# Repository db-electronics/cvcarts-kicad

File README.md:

# Copyright and Disclaimer
Copyright: René Richard

This documentation describes Open Hardware and is licensed under the
CERN OHL v. 1.2.

You may redistribute and modify this documentation under the terms of the
CERN OHL v.1.2. (http://ohwr.org/cernohl). This documentation is distributed
WITHOUT ANY EXPRESS OR IMPLIED WARRANTY, INCLUDING OF
MERCHANTABILITY, SATISFACTORY QUALITY AND FITNESS FOR A
PARTICULAR PURPOSE. Please see the CERN OHL v.1.2 for applicable
conditions

# Colecovision Cartridge
This KiCad project is a 32KB Colecovision ROM cartridge.

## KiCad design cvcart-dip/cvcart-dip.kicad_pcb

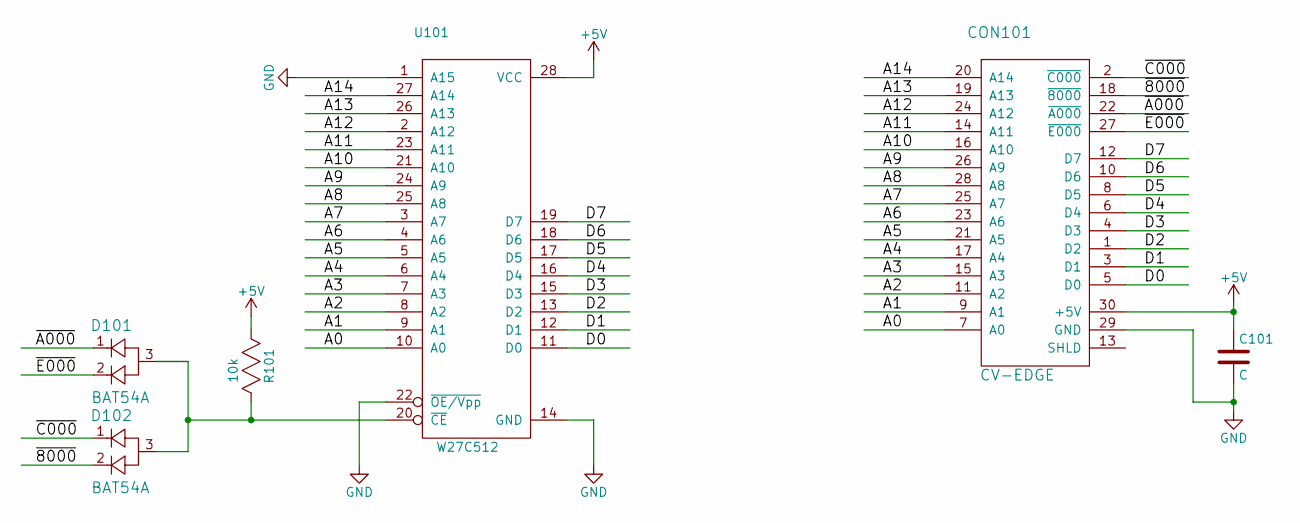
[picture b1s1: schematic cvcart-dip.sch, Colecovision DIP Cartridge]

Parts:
C101: C; 0603
CON101: CV-EDGE
D101, D102: BAT54A; SOT23
R101: 10k; 0603
U101: W27C512; DIP-28-600MIL

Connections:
+5V: C101.1, CON101.30 (+5V), R101.1, U101.28 (VCC)
/A0: CON101.7 (A0), U101.10 (A0)
/A1: CON101.9 (A1), U101.9 (A1)
/A2: CON101.11 (A2), U101.8 (A2)
/A3: CON101.15 (A3), U101.7 (A3)
/A4: CON101.17 (A4), U101.6 (A4)
/A5: CON101.21 (A5), U101.5 (A5)
/A6: CON101.23 (A6), U101.4 (A6)
/A7: CON101.25 (A7), U101.3 (A7)
/A8: CON101.28 (A8), U101.25 (A8)
/A9: CON101.26 (A9), U101.24 (A9)
/A10: CON101.16 (A10), U101.21 (A10)
/A11: CON101.14 (A11), U101.23 (A11)
/A12: CON101.24 (A12), U101.2 (A12)
/A13: CON101.19 (A13), U101.26 (A13)
/A14: CON101.20 (A14), U101.27 (A14)
/D0: CON101.5 (D0), U101.11 (D0)
/D1: CON101.3 (D1), U101.12 (D1)
/D2: CON101.1 (D2), U101.13 (D2)
/D3: CON101.4 (D3), U101.15 (D3)
/D4: CON101.6 (D4), U101.16 (D4)
/D5: CON101.8 (D5), U101.17 (D5)
/D6: CON101.10 (D6), U101.18 (D6)
/D7: CON101.12 (D7), U101.19 (D7)
/~8000: CON101.18 (~8000), D102.2
/~A000: CON101.22 (~A000), D101.1
/~C000: CON101.2 (~C000), D102.1
/~E000: CON101.27 (~E000), D101.2
GND: C101.2, CON101.29 (GND), U101.1 (A15), U101.14 (GND), U101.22 (~OE/Vpp)
unnamed: D101.3, D102.3, R101.2, U101.20 (~CE)

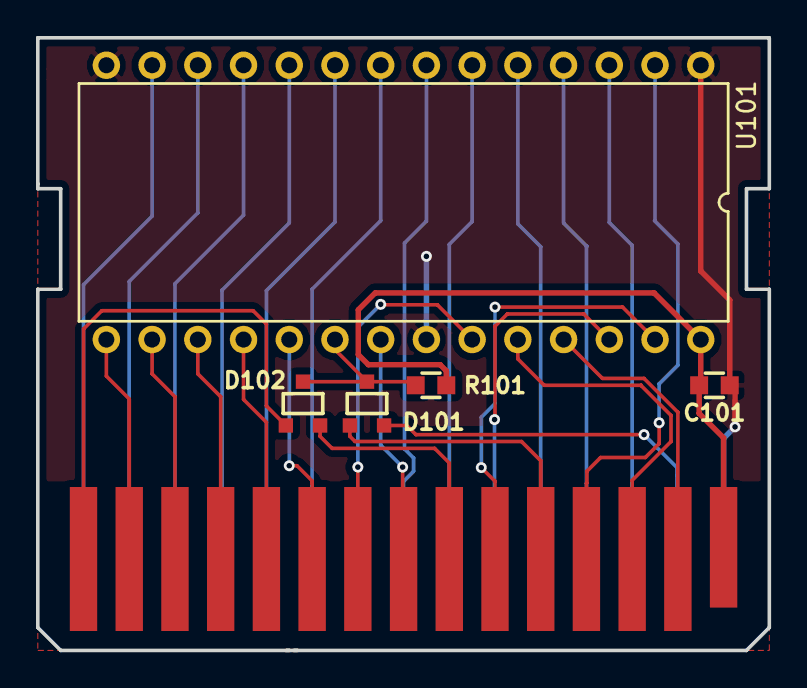
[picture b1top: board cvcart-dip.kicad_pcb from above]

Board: 2 copper layers, 40.6 x 34.0 mm, 6 parts (0 on the bottom side), 30 nets.

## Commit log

2017-02-07 Create license
2017-02-07 first real project in KiCad
2017-02-08 working on schematic
2017-02-09 netlist and pcb work
2017-02-10 routing traces
2017-02-18 layout work, missing ground plane
2017-02-20 added ground pours and keepouts
2017-10-16 added license notice to schematic
2017-10-16 fully licensed as CERN OHL v.1.2
2017-10-16 fixed sch pdf paper size

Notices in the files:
cvcart-dip/cvcart-dip.kicad_pcb:
Licensed under CERN OHL v.1.2”
